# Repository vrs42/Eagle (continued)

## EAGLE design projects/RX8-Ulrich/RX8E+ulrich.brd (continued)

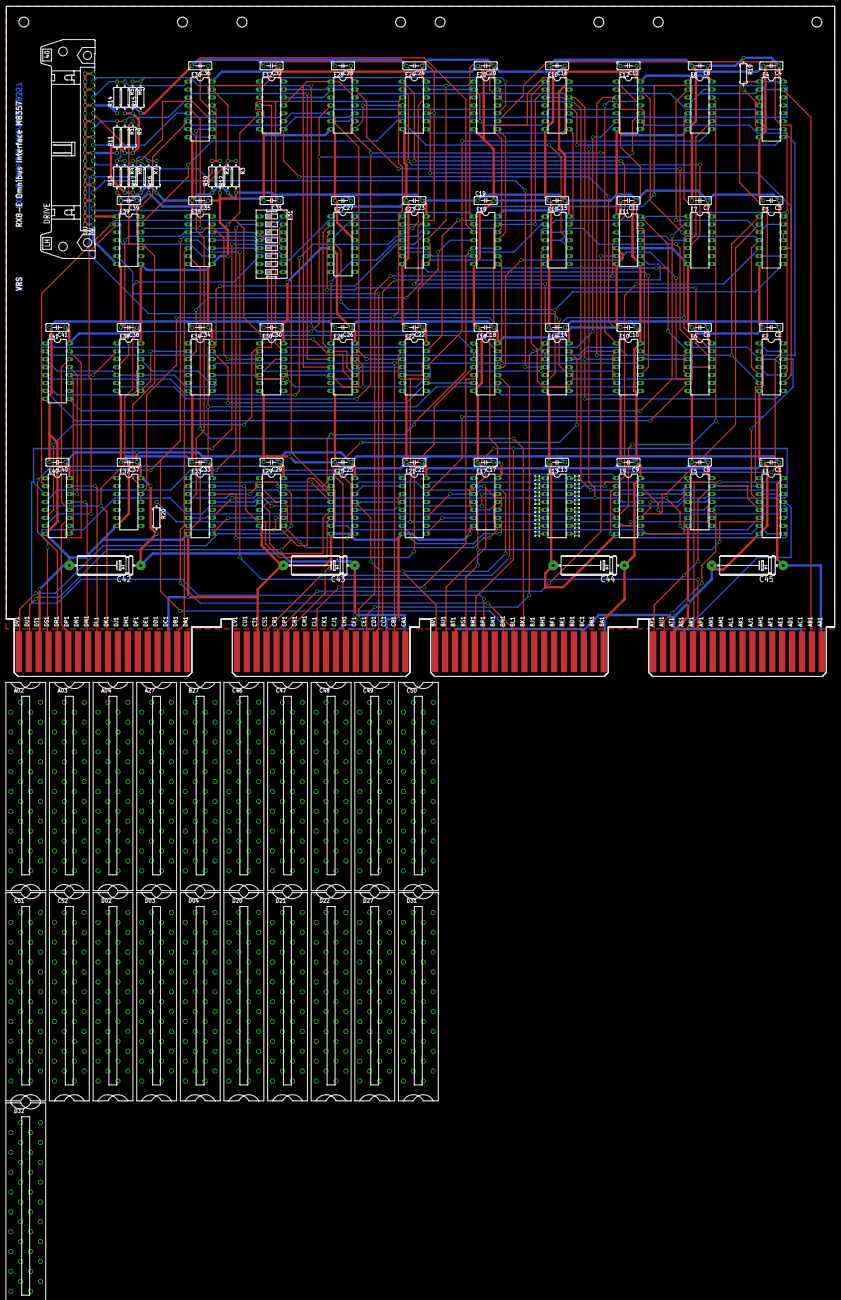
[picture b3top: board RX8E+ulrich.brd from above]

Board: 2 copper layers, 265.3 x 214.6 mm, 145 parts (0 on the bottom side), 290 nets.

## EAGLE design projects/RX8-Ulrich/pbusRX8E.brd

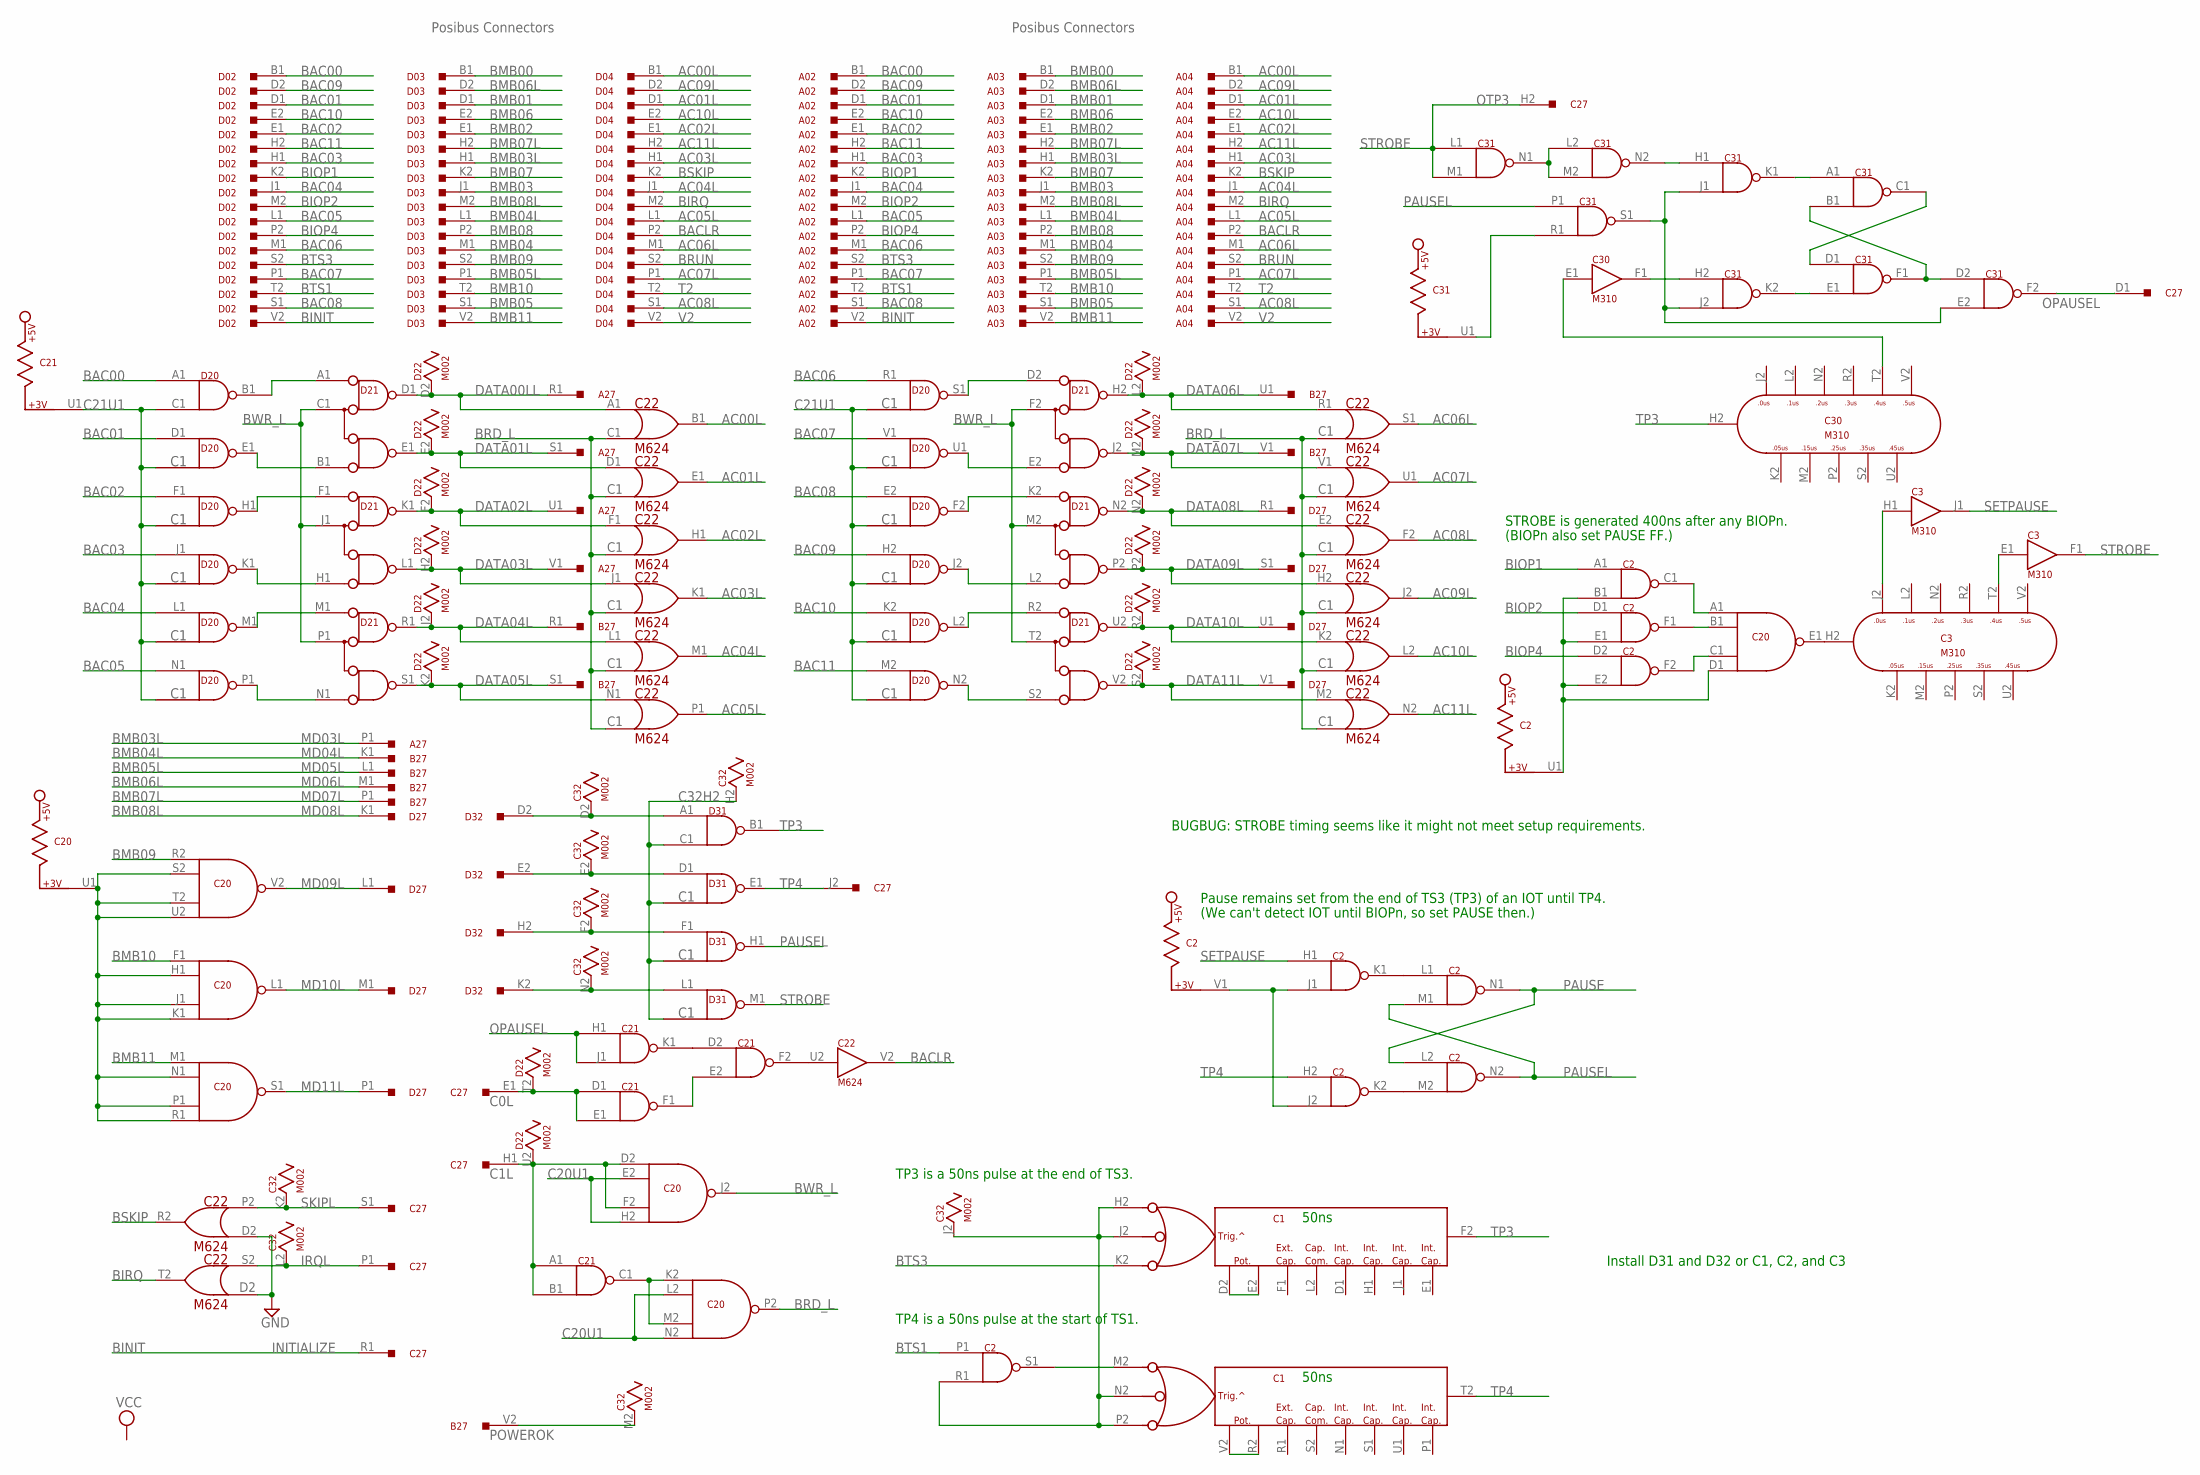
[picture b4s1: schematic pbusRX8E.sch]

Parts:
A02, A03, A04: M903; H807
A27: M916; H807
B27: M916; H807
C1: M302; H807
C2, C21, C31: M113; H807
C3, C30: M310; H807
C20: M617; H807
C22: M624; H807
C27: M916; H807
C32: M002; H807
D02, D03, D04, D32: M903; H807
D20, D31: M101; H807
D21: M623; H807
D22: M002; H807
D27: M916; H807

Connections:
AC00L: A04.B1, C22.B1 (OUT), D04.B1
AC01L: A04.D1, C22.E1 (OUT), D04.D1
AC02L: A04.E1, C22.H1 (OUT), D04.E1
AC03L: A04.H1, C22.K1 (OUT), D04.H1
AC04L: A04.J1, C22.M1 (OUT), D04.J1
AC05L: A04.L1, C22.P1 (OUT), D04.L1
AC06L: A04.M1, C22.S1 (OUT), D04.M1
AC07L: A04.P1, C22.U1 (OUT), D04.P1
AC08L: A04.S1, C22.F2 (OUT), D04.S1
AC09L: A04.D2, C22.J2 (OUT), D04.D2
AC10L: A04.E2, C22.L2 (OUT), D04.E2
AC11L: A04.H2, C22.N2 (OUT), D04.H2
BAC00: A02.B1, D02.B1, D20.A1 (IN1)
BAC01: A02.D1, D02.D1, D20.D1 (IN)
BAC02: A02.E1, D02.E1, D20.F1 (IN)
BAC03: A02.H1, D02.H1, D20.J1 (IN)
BAC04: A02.J1, D02.J1, D20.L1 (IN)
BAC05: A02.L1, D02.L1, D20.N1 (IN)
BAC06: A02.M1, D02.M1, D20.R1 (IN)
BAC07: A02.P1, D02.P1, D20.V1 (IN)
BAC08: A02.S1, D02.S1, D20.E2 (IN)
BAC09: A02.D2, D02.D2, D20.H2 (IN)
BAC10: A02.E2, D02.E2, D20.K2 (IN)
BAC11: A02.H2, D02.H2, D20.M2 (IN)
BACLR: A04.P2, C22.V2 (OUT), D04.P2
BINIT: A02.V2, C27.R1, D02.V2
BIOP1: A02.K2, C2.A1 (IN1), D02.K2
BIOP2: A02.M2, C2.D1 (IN1), D02.M2
BIOP4: A02.P2, C2.D2 (IN1), D02.P2
BIRQ: A04.M2, C22.T2 (OUT), D04.M2
BMB00: A03.B1, D03.B1
BMB01: A03.D1, D03.D1
BMB02: A03.E1, D03.E1
BMB03: A03.J1, D03.J1
BMB03L: A03.H1, A27.P1, D03.H1
BMB04: A03.M1, D03.M1
BMB04L: A03.L1, B27.K1, D03.L1
BMB05: A03.S1, D03.S1
BMB05L: A03.P1, B27.L1, D03.P1
BMB06: A03.E2, D03.E2
BMB06L: A03.D2, B27.M1, D03.D2
BMB07: A03.K2, D03.K2
BMB07L: A03.H2, B27.P1, D03.H2
BMB08: A03.P2, D03.P2
BMB08L: A03.M2, D03.M2, D27.K1
BMB09: A03.S2, C20.R2 (IN1), D03.S2
BMB10: A03.T2, C20.F1 (IN1), D03.T2
BMB11: A03.V2, C20.M1 (IN1), D03.V2
BRD_L: C20.P2 (OUT), C22.C1 (IN2)
BRUN: A04.S2, D04.S2
BSKIP: A04.K2, C22.R2 (OUT), D04.K2
BTS1: A02.T2, C2.P1 (IN1), D02.T2
BTS3: A02.S2, C1.K2, D02.S2
BWR_L: C20.J2 (OUT), D21.C1 (C), D21.F2 (C), D21.J1 (C), D21.M2 (C), D21.P1 (C), D21.T2 (C)
C0L: C21.D1 (IN1), C21.E1 (IN2), C27.E1, D22.T2
C1L: C20.D2 (IN1), C20.F2 (IN3), C21.A1 (IN1), C21.B1 (IN2), C27.H1, D22.U2
C20U1: C20.E2 (IN2), C20.H1 (IN2), C20.H2 (IN4), C20.J1 (IN3), C20.K1 (IN4), C20.L2 (IN2), C20.N1 (IN2), C20.N2 (IN4), C20.P1 (IN3), C20.R1 (IN4), C20.S2 (IN2), C20.T2 (IN3), C20.U1, C20.U2 (IN4)
C21U1: C21.U1, D20.C1 (IN2)
C32H2: C32.H2, D31.C1 (IN2)
DATA00LL: A27.R1, C22.A1 (IN1), D21.D1 (D), D22.D2
DATA01L: A27.S1, C22.D1 (IN), D21.E1 (E), D22.E2
DATA02L: A27.U1, C22.F1 (IN), D21.K1 (D), D22.F2
DATA03L: A27.V1, C22.J1 (IN), D21.L1 (E), D22.H2
DATA04L: B27.R1, C22.L1 (IN), D21.R1 (D), D22.J2
DATA05L: B27.S1, C22.N1 (IN), D21.S1 (E), D22.K2
DATA06L: B27.U1, C22.R1 (IN), D21.H2 (D), D22.L2
DATA07L: B27.V1, C22.V1 (IN), D21.J2 (E), D22.M2
DATA08L: C22.E2 (IN), D21.N2 (D), D22.N2, D27.R1
DATA09L: C22.H2 (IN), D21.P2 (E), D22.P2, D27.S1
DATA10L: C22.K2 (IN), D21.U2 (D), D22.R2, D27.U1
DATA11L: C22.M2 (IN), D21.V2 (E), D22.S2, D27.V1
GND: A02.A1 (GND), A02.C1 (GND), A02.C2 (GND), A02.F1 (GND), A02.F2 (GND), A02.J2 (GND), A02.K1 (GND), A02.L2 (GND), A02.N1 (GND), A02.N2 (GND), A02.R1 (GND), A02.R2 (GND), A02.T1 (GND), A02.U2 (GND), A03.A1 (GND), A03.C1 (GND), A03.C2 (GND), A03.F1 (GND), A03.F2 (GND), A03.J2 (GND), A03.K1 (GND), A03.L2 (GND), A03.N1 (GND), A03.N2 (GND), A03.R1 (GND), A03.R2 (GND), A03.T1 (GND), A03.U2 (GND), A04.A1 (GND), A04.C1 (GND), A04.C2 (GND), A04.F1 (GND), A04.F2 (GND), A04.J2 (GND), A04.K1 (GND), A04.L2 (GND), A04.N1 (GND), A04.N2 (GND), A04.R1 (GND), A04.R2 (GND), A04.T1 (GND), A04.U2 (GND), C1.C2 (GND), C1.T1 (GND), C2.C2 (GND), C2.T1 (GND), C3.C2 (GND), C3.T1 (GND), C20.C2 (GND), C20.T1 (GND), C21.C2 (GND), C21.T1 (GND), C22.C2 (GND), C22.D2 (IN2), C22.T1 (GND), C30.C2 (GND), C30.T1 (GND), C31.C2 (GND), C31.T1 (GND), C32.C2 (GND), D02.A1 (GND), D02.C1 (GND), D02.C2 (GND), D02.F1 (GND), D02.F2 (GND), D02.J2 (GND), D02.K1 (GND), D02.L2 (GND), D02.N1 (GND), D02.N2 (GND), D02.R1 (GND), D02.R2 (GND), D02.T1 (GND), D02.U2 (GND), D03.A1 (GND), D03.C1 (GND), D03.C2 (GND), D03.F1 (GND), D03.F2 (GND), D03.J2 (GND), D03.K1 (GND), D03.L2 (GND), D03.N1 (GND), D03.N2 (GND), D03.R1 (GND), D03.R2 (GND), D03.T1 (GND), D03.U2 (GND), D04.A1 (GND), D04.C1 (GND), D04.C2 (GND), D04.F1 (GND), D04.F2 (GND), D04.J2 (GND), D04.K1 (GND), D04.L2 (GND), D04.N1 (GND), D04.N2 (GND), D04.R1 (GND), D04.R2 (GND), D04.T1 (GND), D04.U2 (GND), D20.C2 (GND), D20.T1 (GND), D21.C2 (GND), D21.T1 (GND), D21.U1 (GND), D21.V1 (GND), D22.C2 (GND), D31.C2 (GND), D31.T1 (GND), D32.A1 (GND), D32.C1 (GND), D32.C2 (GND), D32.F1 (GND), D32.F2 (GND), D32.J2 (GND), D32.K1 (GND), D32.L2 (GND), D32.N1 (GND), D32.N2 (GND), D32.R1 (GND), D32.R2 (GND), D32.T1 (GND), D32.U2 (GND)
IRQL: C22.S2 (IN), C27.P1, C32.L2
MD09L: C20.V2 (OUT), D27.L1
MD10L: C20.L1 (OUT), D27.M1
MD11L: C20.S1 (OUT), D27.P1
unnamed: D20.B1 (OUT), D21.A1 (A)
unnamed: D20.E1 (OUT), D21.B1 (B)
unnamed: D20.H1 (OUT), D21.F1 (A)
unnamed: D20.K1 (OUT), D21.H1 (B)
unnamed: D20.P1 (OUT), D21.N1 (B)
unnamed: D20.M1 (OUT), D21.M1 (A)
unnamed: C20.K2 (IN1), C20.M2 (IN3), C21.C1 (OUT)
unnamed: D20.N2 (OUT), D21.S2 (B)
unnamed: C32.D2, D31.A1 (IN1), D32.D2
unnamed: D20.J2 (OUT), D21.L2 (B)
unnamed: D20.U1 (OUT), D21.E2 (B)
unnamed: D20.S1 (OUT), D21.D2 (A)
unnamed: D20.F2 (OUT), D21.K2 (A)
unnamed: D20.L2 (OUT), D21.R2 (A)
unnamed: C32.E2, D31.D1 (IN), D32.E2
unnamed: C32.F2, D31.F1 (IN), D32.H2
unnamed: C32.N2, D31.L1 (IN), D32.K2
unnamed: C31.E2 (IN2), C31.J1 (IN2), C31.J2 (IN2), C31.S1 (OUT)
unnamed: C21.E2 (IN2), C21.F1 (OUT)
unnamed: C21.D2 (IN1), C21.K1 (OUT)
unnamed: C31.C1 (OUT), C31.D1 (IN1)
unnamed: C31.B1 (IN2), C31.D2 (IN1), C31.F1 (OUT)
unnamed: C21.F2 (OUT), C22.U2 (IN)
unnamed: C30.E1 (IN), C30.T2
unnamed: C30.F1 (OUT), C31.H2 (IN1)
unnamed: C31.L2 (IN1), C31.M2 (IN2), C31.N1 (OUT)
unnamed: C3.H2, C20.E1 (OUT)
unnamed: C31.H1 (IN1), C31.N2 (OUT)
unnamed: C31.A1 (IN1), C31.K1 (OUT)
unnamed: C31.E1 (IN2), C31.K2 (OUT)
unnamed: C3.E1 (IN), C3.T2
unnamed: C2.F2 (OUT), C20.C1 (IN3)
unnamed: C2.C1 (OUT), C20.A1 (IN1)
unnamed: C2.F1 (OUT), C20.B1 (IN2)
unnamed: C1.D2, C1.E2
unnamed: C1.M2 (H2), C2.S1 (OUT)
unnamed: C1.R2 (E2), C1.V2 (D2)
unnamed: C3.H1 (IN), C3.J2
unnamed: C2.K1 (OUT), C2.L1 (IN1)
unnamed: C1.H2, C1.J2, C1.N2 (J2), C1.P2 (K2), C2.R1 (IN2), C32.J2
unnamed: C2.K2 (OUT), C2.M2 (IN2)
unnamed: C31.R1 (IN2), C31.U1
unnamed: C2.B1 (IN2), C2.E1 (IN2), C2.E2 (IN2), C2.U1, C20.D1 (IN4)
unnamed: C2.J1 (IN2), C2.J2 (IN2), C2.V1
OPAUSEL: C21.H1 (IN1), C21.J1 (IN2), C27.D1, C31.F2 (OUT)
PAUSE: C2.L2 (IN1), C2.N1 (OUT)
PAUSEL: C2.M1 (IN2), C2.N2 (OUT), C31.P1 (IN1), D31.H1 (OUT)
POWEROK: B27.V2, C32.M2
SETPAUSE: C2.H1 (IN1), C3.J1 (OUT)
SKIPL: C22.P2 (IN1), C27.S1, C32.K2
STROBE: C3.F1 (OUT), C27.H2, C31.L1 (IN1), C31.M1 (IN2), D31.M1 (OUT)
T2: A04.T2, D04.T2
TP3: C1.F2, C30.H2, D31.B1 (OUT)
TP4: C1.T2 (F2), C2.H2 (IN1), C27.J2, D31.E1 (OUT)
V2: A04.V2, D04.V2
VCC: C1.A2 (VCC), C2.A2 (VCC), C3.A2 (VCC), C20.A2 (VCC), C21.A2 (VCC), C22.A2 (VCC), C30.A2 (VCC), C31.A2 (VCC), C32.A2 (VCC), D20.A2 (VCC), D21.A2 (VCC), D22.A2 (VCC), D31.A2 (VCC)

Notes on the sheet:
Posibus Connectors
MD03L
MD04L
MD05L
MD06L
MD07L
MD08L
INITIALIZE
OTP3
TP3 is a 50ns pulse at the end of TS3.
STROBE is generated 400ns after any BIOPn.
TP4 is a 50ns pulse at the start of TS1.
BUGBUG: STROBE timing seems like it might not meet setup requirements.
50ns
Pause remains set from the end of TS3 (TP3) of an IOT until TP4.
(We can't detect IOT until BIOPn, so set PAUSE then.)
Install D31 and D32 or C1, C2, and C3
(BIOPn also set PAUSE FF.)

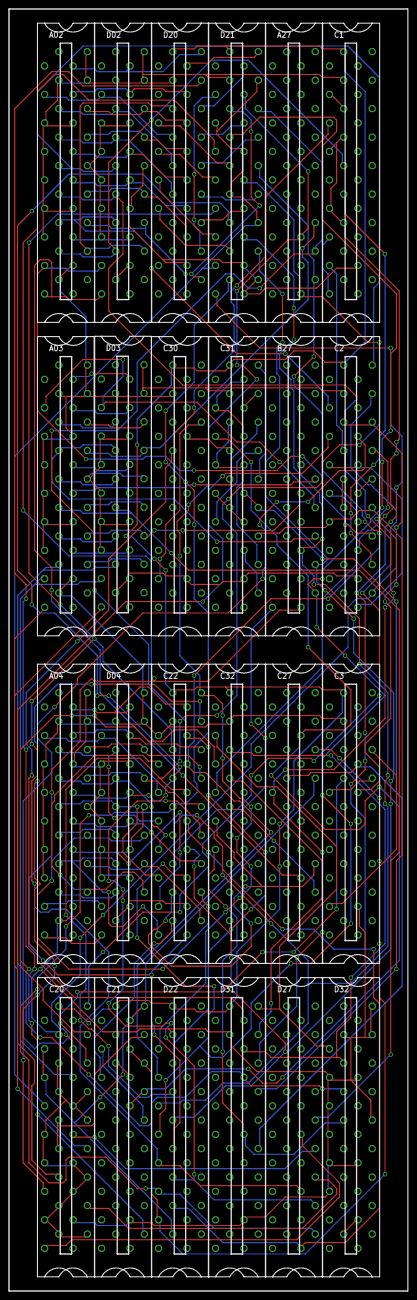
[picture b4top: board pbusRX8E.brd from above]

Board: 2 copper layers, 88.9 x 285.8 mm, 24 parts (0 on the bottom side), 132 nets.
